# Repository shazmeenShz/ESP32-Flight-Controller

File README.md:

# ESP32 Flight Controller

A 4-layer ESP32 flight-controller PCB, designed in KiCad 8 and manufactured as Rev 2.

The board is built around an **ESP32-WROOM-32E**. It takes a LiPo on an XT30, makes 5 V with an MP1584 and 3.3 V with an AMS1117, and brings out USB-C programming, an MPU-6050, GPS, and receiver headers. This repository is the hardware: schematics, PCB, Gerbers, BOM, and photos. There is no flight firmware here.

---

## Hardware

| | |
| --- | --- |
| MCU | ESP32-WROOM-32E (Wi-Fi and Bluetooth) |
| IMU | MPU-6050, I²C |
| USB | Type-C, CH340C USB-UART |
| Battery | LiPo on XT30 (J1) |
| 5 V | MP1584 buck (U6) |
| 3.3 V | AMS1117-3.3 (U2) |
| Status | WS2812B and an active buzzer |
| Buttons | BOOT (SW2) and RESET (SW1) |
| Board | 4-layer, 1.6 mm |
| CAD | KiCad 8 |

Power path:

```text
LiPo (XT30) → MP1584 → 5 V → AMS1117-3.3 → 3.3 V → ESP32
```

Copper is 1 oz (0.035 mm) on all four layers. The Rev 2 Gerbers name the inner layers `GND` and `POWER`.

### Connectors

| Ref | What it is |
| --- | --- |
| J1 | Battery, XT30 |
| J3 | iBUS / SBUS receiver, 1×3 |
| J4 | PWM receiver, 1×8 |
| J5 | Motor outputs, 1×5 |
| J6 | GPS UART, 1×4 |
| J9 | USB-C |
| — | ADC battery-voltage divider |

---

## Revisions

**Rev 1** is the first design, in the repository root (`flight_controller.kicad_sch`, `flight_controller.kicad_pcb`, `flight_controller_BOM.csv`, and `ESP32-FLight-Controller-Gerber.zip`).

**Rev 2** is the board that was manufactured. Files are under `Rev2/`. Compared with the Rev 1 BOM, Rev 2 adds:

- USBLC6-2SC6 (U5) on USB
- SM6T24A (D4) and a second Schottky (D5)
- the NextPCB logo footprint on the PCB

---

## Rev 2 photos

KiCad renders and copper views:

### Rev 1 views

---

## What is in this repo

```text
ESP32-Flight-Controller
├── flight_controller.kicad_pro      Rev 1 KiCad project
├── flight_controller.kicad_sch
├── flight_controller.kicad_pcb
├── flight_controller_BOM.csv
├── ESP32-FLight-Controller-Gerber.zip
├── pcb.png
├── schematic.png
├── 3D_front.png
├── 3D_back.png
├── LICENSE
├── README.md
└── Rev2/
    ├── KiCad/                       schematic, PCB, NextPCB logo footprint
    ├── Gerbers/                     copper, mask, paste, silk, edge, drill
    ├── BOM/flight_controller_bom.csv
    ├── Documentation/               drill map
    └── Images/                      photos, renders, copper plots, logo
```

Open `Rev2/KiCad/flight_controller_rev2.kicad_pro` in KiCad 8. The Gerber set in `Rev2/Gerbers/` is what was sent for manufacturing.

---

## Manufacturing support

<p align="center">
  
</p>

Thank you to [NextPCB](https://www.nextpcb.com) for manufacturing the Rev 2 PCB. That support took the design from KiCad to a finished board and made the hands-on testing of this student project possible.

**Manufacturing partner:** [NextPCB](https://www.nextpcb.com)  
**Sponsored revision:** Rev 2

---

## Not on this board yet

These are next hardware steps, not features of the current PCB:

- Barometer (BMP280 / BME280)
- Magnetometer
- Current sensor
- Blackbox logging
- CAN
- Stronger input protection beyond the parts already on Rev 2

---

## Author

**Shazmeen Siddiqui**

B.Tech, Electrical and Computer Engineering, Jamia Millia Islamia

## License

[MIT](LICENSE)

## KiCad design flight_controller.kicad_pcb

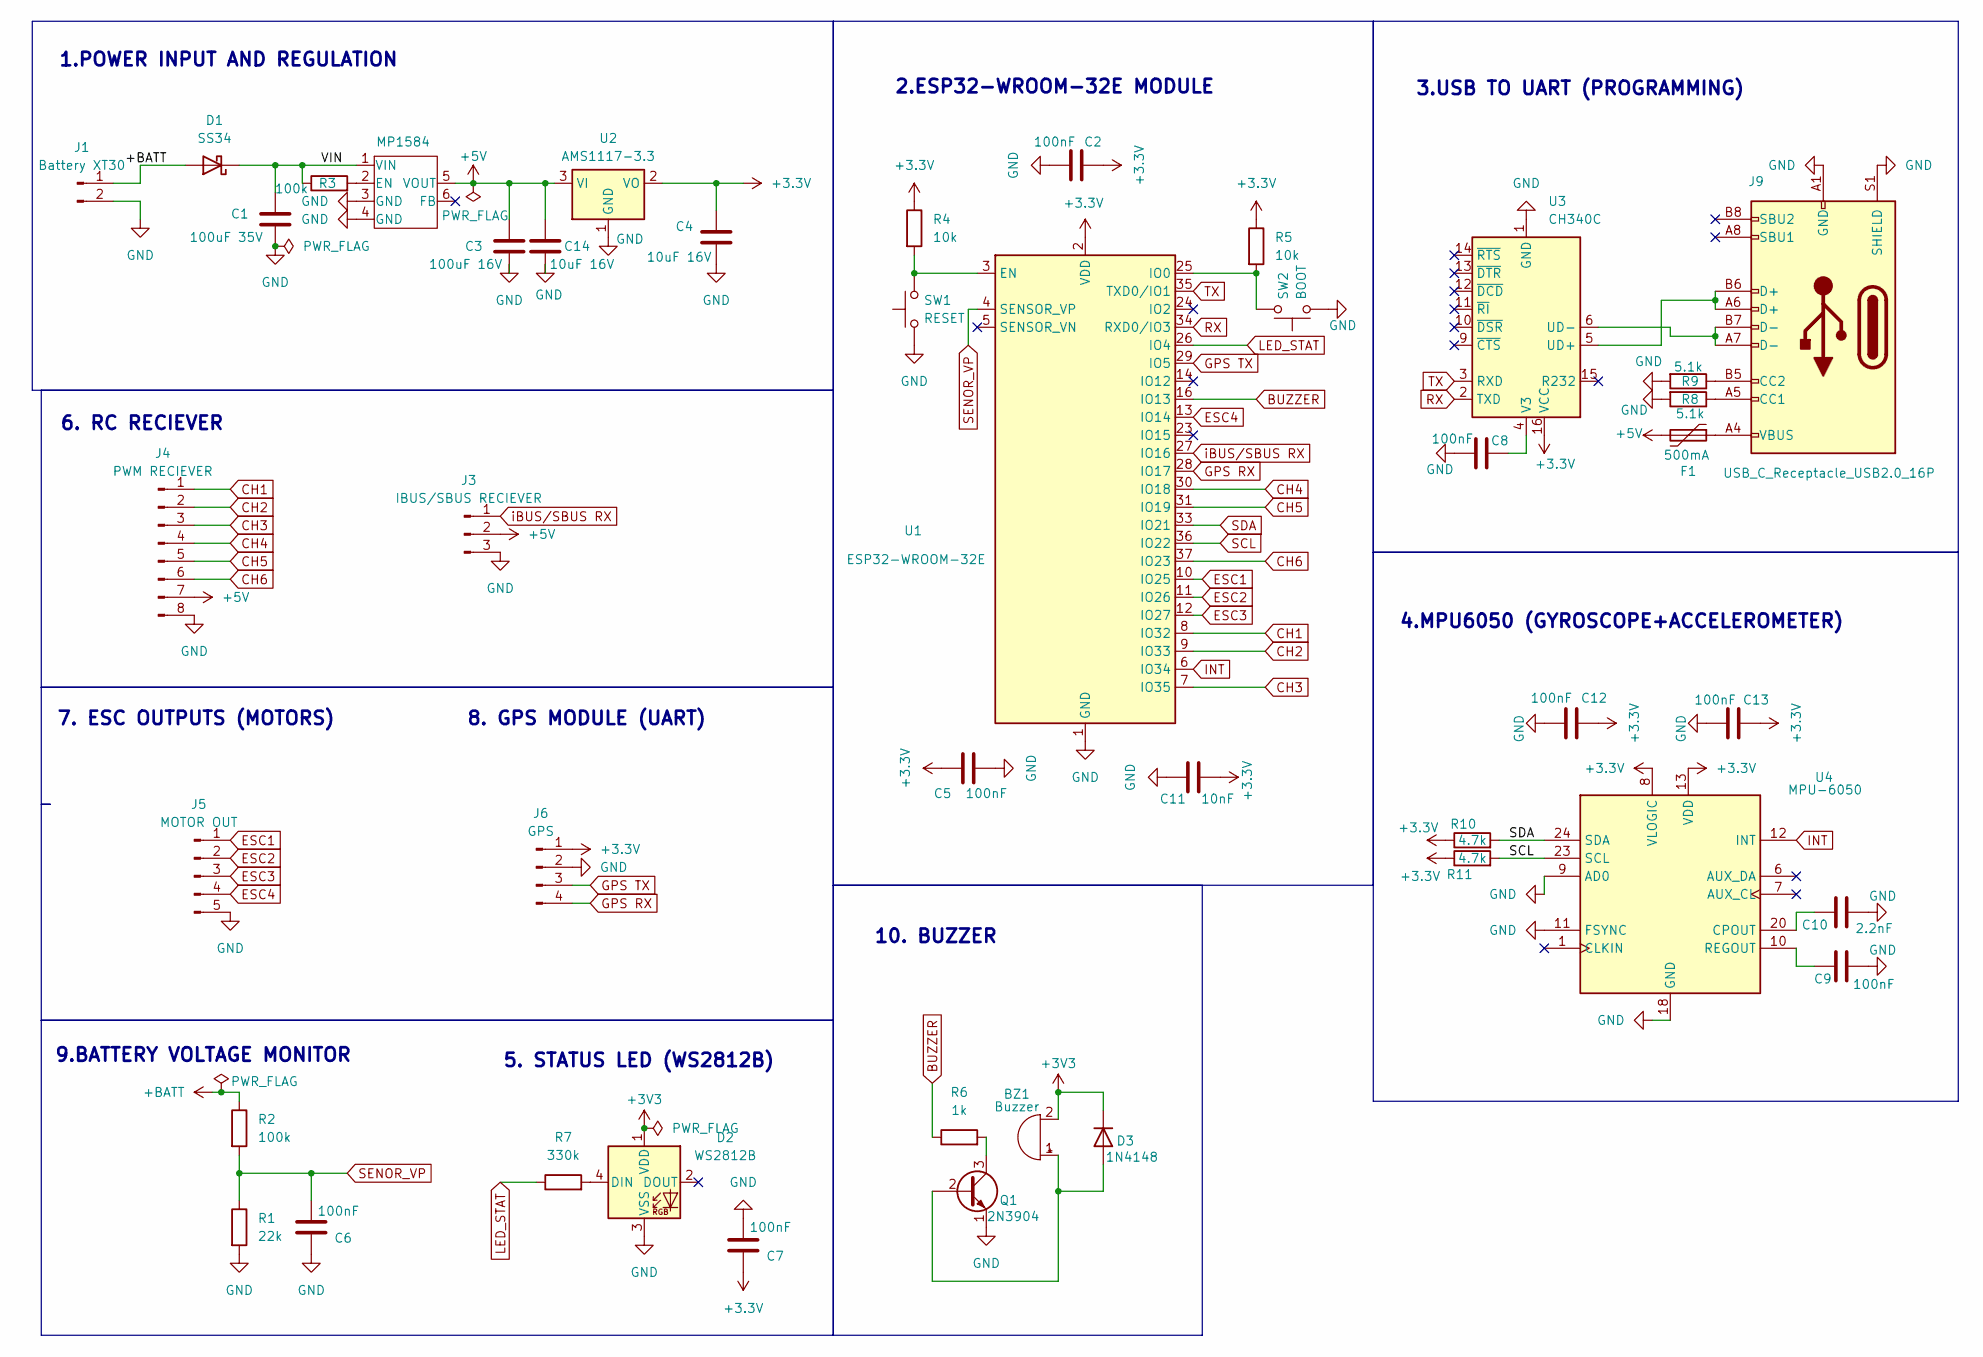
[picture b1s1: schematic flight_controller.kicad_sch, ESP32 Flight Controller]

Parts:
BZ1: Buzzer; Buzzer_12x9.5RM7.6
C1: 100uF 35V; C_Elec_6.3x5.8
C2, C5, C6, C7, C8, C9, C12, C13: 100nF; C_0603_1608Metric
C3: 100uF 16V; C_Elec_6.3x5.8
C4, C14: 10uF 16V; C_0805_2012Metric
C10: 2.2nF; C_0603_1608Metric
C11: 10nF; C_0603_1608Metric
D1: SS34; D_SMA
D2: WS2812B; LED_WS2812B_PLCC4_5.0x5.0mm_P3.2mm
D3: 1N4148; D_SOD-123
F1: 500mA; Fuse_1206_3216Metric
J1: Battery XT30; AMASS_XT30PW-M_1x02_P2.50mm_Horizontal
J3: IBUS/SBUS RECIEVER; PinHeader_1x03_P2.54mm_Vertical
J4: PWM RECIEVER; PinHeader_1x08_P2.54mm_Vertical
J5: MOTOR OUT; PinHeader_1x05_P2.54mm_Vertical
J6: GPS; PinHeader_1x04_P2.54mm_Vertical
J9: USB_C_Receptacle_USB2.0_16P; USB_C_Receptacle_GCT_USB4105-xx-A_16P_TopMnt_Horizontal
MP1584: SOIC-8-1EP_3.9x4.9mm_P1.27mm_EP2.29x3mm
Q1: 2N3904; SOT-23
R1: 22k; R_0603_1608Metric
R2, R3: 100k; R_0603_1608Metric
R4, R5: 10k; R_0603_1608Metric
R6: 1k; R_0603_1608Metric
R7: 330k; R_0603_1608Metric
R8, R9: 5.1k; R_0603_1608Metric
R10, R11: 4.7k; R_0603_1608Metric
SW1: RESET; SW_SPST_EVQP7C
SW2: BOOT; SW_SPST_EVQP7C
U1: ESP32-WROOM-32E; ESP32-WROOM-32D
U2: AMS1117-3.3; SOT-223-3_TabPin2
U3: CH340C; SOIC-16_3.9x9.9mm_P1.27mm
U4: MPU-6050; InvenSense_QFN-24_4x4mm_P0.5mm

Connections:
+3.3V: C2.1, C4.1, C5.1, C7.1, C11.1, C12.1, C13.1, J6.1, R4.1, R5.1, R10.1, R11.1, U1.2 (VDD), U2.2 (VO), U3.16 (VCC), U4.8 (VLOGIC), U4.13 (VDD)
+3V3: BZ1.2 (-), D2.1 (VDD), D3.1 (K)
+5V: C3.1, C14.1, F1.2, J3.2, J4.7, MP1584.5 (VOUT), U2.3 (VI)
+BATT: D1.2 (A), J1.1, R2.1
/VIN: C1.1, D1.1 (K), MP1584.1 (VIN), R3.1
BUZZER: R6.1, U1.16 (IO13)
CH1: J4.1, U1.8 (IO32)
CH2: J4.2, U1.9 (IO33)
CH3: J4.3, U1.7 (IO35)
CH4: J4.4, U1.30 (IO18)
CH5: J4.5, U1.31 (IO19)
CH6: J4.6, U1.37 (IO23)
ESC1: J5.1, U1.10 (IO25)
ESC2: J5.2, U1.11 (IO26)
ESC3: J5.3, U1.12 (IO27)
ESC4: J5.4, U1.13 (IO14)
GND: C1.2, C2.2, C3.2, C4.2, C5.2, C6.1, C7.2, C8.2, C9.2, C10.2, C11.2, C12.2, C13.2, C14.2, D2.3 (VSS), J1.2, J3.3, J4.8, J5.5, J6.2, J9.A1 (GND), J9.A12 (GND), J9.B1 (GND), J9.B12 (GND), J9.S1 (SHIELD), MP1584.3 (GND), MP1584.4 (GND), Q1.1 (E), R1.2, R8.2, R9.2, SW1.1, SW2.1, U1.1 (GND), U1.15 (GND), U1.38 (GND), U1.39 (GND), U2.1 (GND), U3.1 (GND), U4.9 (AD0), U4.11 (FSYNC), U4.18 (GND)
GPS RX: J6.4, U1.28 (IO17)
GPS TX: J6.3, U1.29 (IO5)
INT: U1.6 (IO34), U4.12 (INT)
LED_STAT: R7.1, U1.26 (IO4)
unnamed: BZ1.1 (+), D3.2 (A), Q1.2 (B)
unnamed: D2.4 (DIN), R7.2
unnamed: F1.1, J9.A4 (VBUS), J9.A9 (VBUS), J9.B4 (VBUS), J9.B9 (VBUS)
unnamed: J9.A5 (CC1), R8.1
unnamed: J9.B5 (CC2), R9.1
unnamed: MP1584.2 (EN), R3.2
unnamed: Q1.3 (C), R6.2
unnamed: R4.2, SW1.2, U1.3 (EN)
unnamed: R5.2, SW2.2, U1.25 (IO0)
unnamed: J9.A6 (D+), J9.B6 (D+), U3.5 (UD+)
unnamed: J9.A7 (D-), J9.B7 (D-), U3.6 (UD-)
unnamed: C8.1, U3.4 (V3)
unnamed: C10.1, U4.20 (CPOUT)
unnamed: C9.1, U4.10 (REGOUT)
RX: U1.34 (RXD0/IO3), U3.2 (TXD)
SCL: R11.2, U1.36 (IO22), U4.23 (SCL)
SDA: R10.2, U1.33 (IO21), U4.24 (SDA)
SENOR_VP: C6.2, R1.1, R2.2, U1.4 (SENSOR_VP)
TX: U1.35 (TXD0/IO1), U3.3 (RXD)
iBUS/SBUS RX: J3.1, U1.27 (IO16)

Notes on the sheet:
7. ESC OUTPUTS (MOTORS)
9.BATTERY VOLTAGE MONITOR
2.ESP32-WROOM-32E MODULE
3.USB TO UART (PROGRAMMING)
10. BUZZER
4.MPU6050 (GYROSCOPE+ACCELEROMETER)
6. RC RECIEVER
8. GPS MODULE (UART)
5. STATUS LED (WS2812B)
1.POWER INPUT AND REGULATION

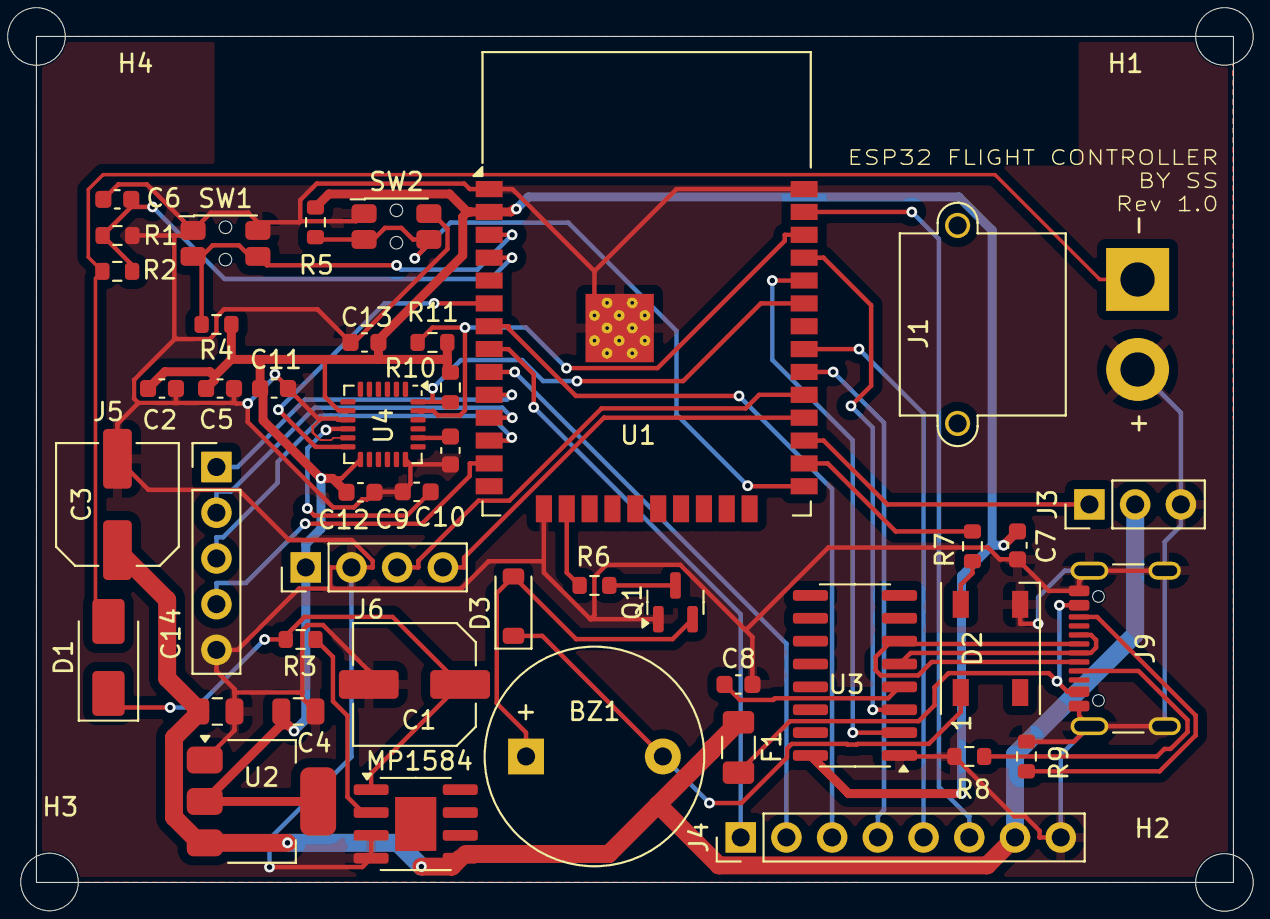
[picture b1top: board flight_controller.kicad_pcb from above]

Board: 4 copper layers, 66.5 x 47.0 mm, 48 parts (0 on the bottom side), 41 nets.

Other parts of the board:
H1, H2, H3, H4: MountingHole_3.2mm_M3

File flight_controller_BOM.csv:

"Reference","Value","Datasheet","Footprint","Qty","DNP"
"BZ1","Buzzer","~","Buzzer_Beeper:Buzzer_12x9.5RM7.6","1",""
"C1","100uF 35V","~","Capacitor_SMD:C_Elec_6.3x5.8","1",""
"C2,C5,C6,C7,C8,C9,C12,C13","100nF","~","Capacitor_SMD:C_0603_1608Metric","8",""
"C3","100uF 16V","~","Capacitor_SMD:C_Elec_6.3x5.8","1",""
"C4,C14","10uF 16V","~","Capacitor_SMD:C_0805_2012Metric","2",""
"C10","2.2nF","~","Capacitor_SMD:C_0603_1608Metric","1",""
"C11","10nF","~","Capacitor_SMD:C_0603_1608Metric","1",""
"D1","SS34","https://www.vishay.com/docs/88751/ss32.pdf","Diode_SMD:D_SMA","1",""
"D2","WS2812B","https://cdn-shop.adafruit.com/datasheets/WS2812B.pdf","LED_SMD:LED_WS2812B_PLCC4_5.0x5.0mm_P3.2mm","1",""
"D3","1N4148","https://assets.nexperia.com/documents/data-sheet/1N4148_1N4448.pdf","Diode_SMD:D_SOD-123","1",""
"F1","500mA","~","Fuse:Fuse_1206_3216Metric","1",""
"J1","Battery XT30","~","Connector_AMASS:AMASS_XT30PW-M_1x02_P2.50mm_Horizontal","1",""
"J3","IBUS/SBUS RECIEVER","~","Connector_PinHeader_2.54mm:PinHeader_1x03_P2.54mm_Vertical","1",""
"J4","PWM RECIEVER","~","Connector_PinHeader_2.54mm:PinHeader_1x08_P2.54mm_Vertical","1",""
"J5","MOTOR OUT","~","Connector_PinHeader_2.54mm:PinHeader_1x05_P2.54mm_Vertical","1",""
"J6","GPS ","~","Connector_PinHeader_2.54mm:PinHeader_1x04_P2.54mm_Vertical","1",""
"J9","USB_C_Receptacle_USB2.0_16P","https://www.usb.org/sites/default/files/documents/usb_type-c.zip","Connector_USB:USB_C_Receptacle_GCT_USB4105-xx-A_16P_TopMnt_Horizontal","1",""
"MP1584","~","","Package_SO:SOIC-8-1EP_3.9x4.9mm_P1.27mm_EP2.29x3mm","1",""
"Q1","2N3904","https://www.onsemi.com/pub/Collateral/2N3903-D.PDF","Package_TO_SOT_SMD:SOT-23","1",""
"R1","22k","~","Resistor_SMD:R_0603_1608Metric","1",""
"R2,R3","100k","~","Resistor_SMD:R_0603_1608Metric","2",""
"R4,R5","10k","~","Resistor_SMD:R_0603_1608Metric","2",""
"R6","1k","~","Resistor_SMD:R_0603_1608Metric","1",""
"R7","330k","~","Resistor_SMD:R_0603_1608Metric","1",""
"R8,R9","5.1k","~","Resistor_SMD:R_0603_1608Metric","2",""
"R10,R11","4.7k","~","Resistor_SMD:R_0603_1608Metric","2",""
"SW1","RESET","~","Button_Switch_SMD:SW_SPST_EVQP7C","1",""
"SW2","BOOT","~","Button_Switch_SMD:SW_SPST_EVQP7C","1",""
"U1","ESP32-WROOM-32E","https://www.espressif.com/sites/default/files/documentation/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","RF_Module:ESP32-WROOM-32D","1",""
"U2","AMS1117-3.3","http://www.advanced-monolithic.com/pdf/ds1117.pdf","Package_TO_SOT_SMD:SOT-223-3_TabPin2","1",""
"U3","CH340C","https://datasheet.lcsc.com/szlcsc/Jiangsu-Qin-Heng-CH340C_C8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","Package_SO:SOIC-16_3.9x9.9mm_P1.27mm","1",""
"U4","MPU-6050","https://invensense.tdk.com/wp-content/uploads/2015/02/MPU-60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","Sensor_Motion:InvenSense_QFN-24_4x4mm_P0.5mm","1",""

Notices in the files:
flight_controller.kicad_pcb:
© 2026
